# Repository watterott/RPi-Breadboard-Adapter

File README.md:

# RPi to Breadboard Adapter
Breadboard Adapter for all Raspberry Pi HAT compatible models (40pin connector).

* Open-Source and released under the [Creative Commons Attribution Share-Alike License](https://creativecommons.org/licenses/by-sa/4.0/).
* **[Documentation on learn.watterott.com](https://learn.watterott.com)**

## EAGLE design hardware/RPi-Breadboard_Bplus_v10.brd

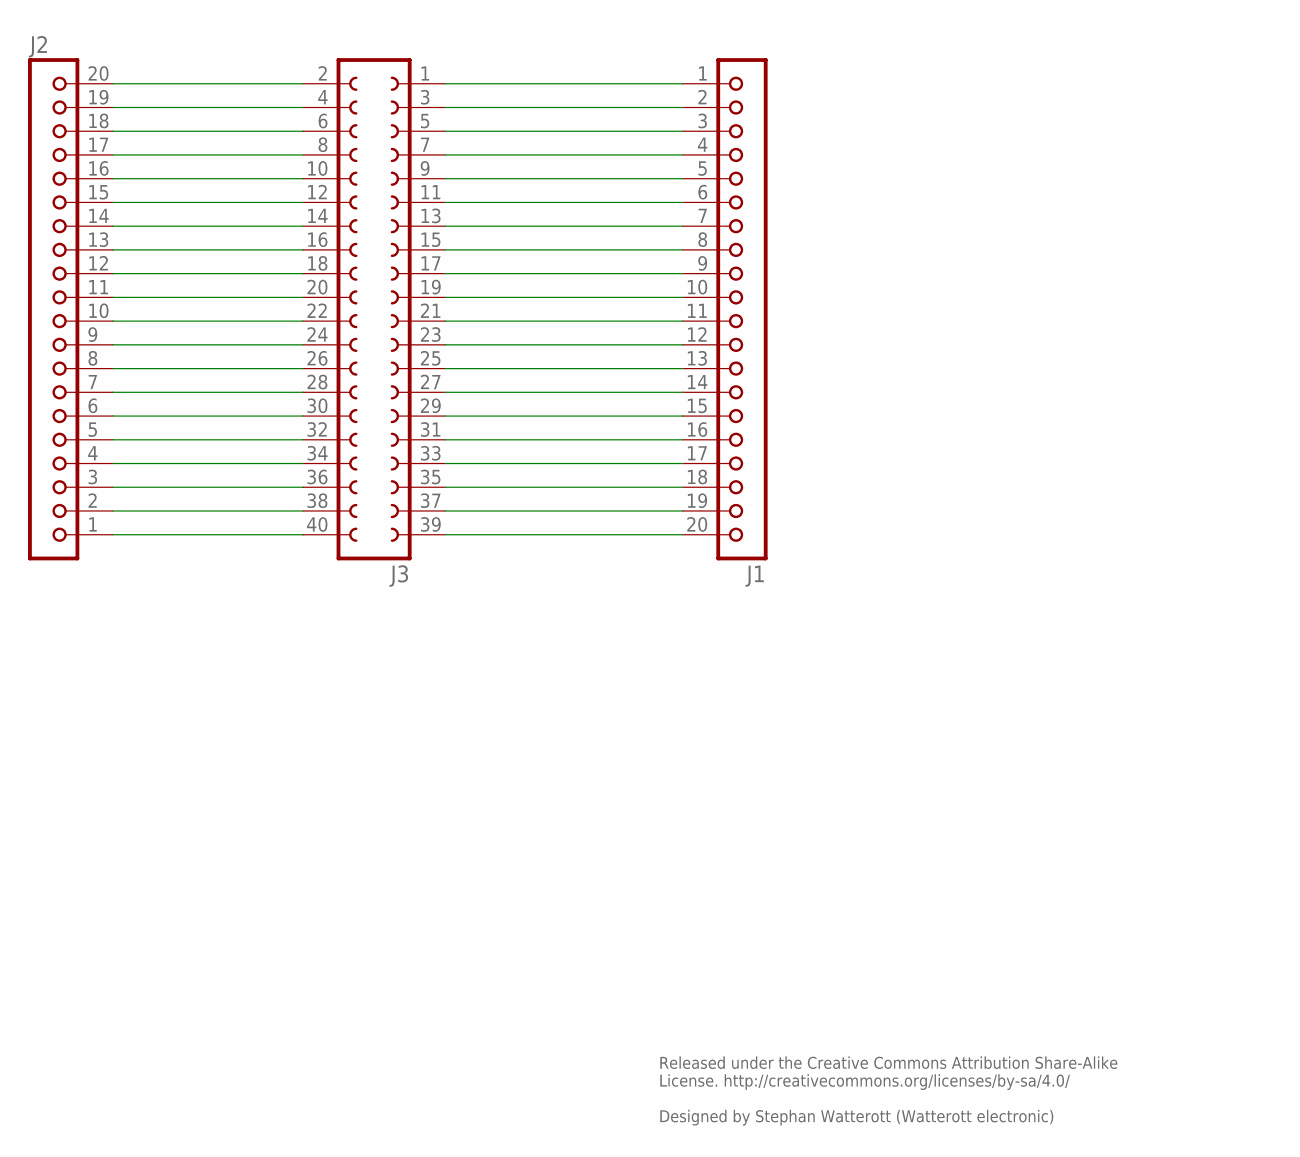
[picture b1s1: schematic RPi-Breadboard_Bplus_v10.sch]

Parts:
J1, J2: JBK20
J3: FE20-2

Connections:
5V: J1.1, J1.2, J3.1, J3.3
GND: J1.3, J1.7, J1.10, J1.15, J1.17, J2.1, J2.8, J2.16, J3.5, J3.10, J3.13, J3.19, J3.26, J3.29, J3.33, J3.40
unnamed: J1.4, J3.7
unnamed: J1.5, J3.9
unnamed: J1.6, J3.11
unnamed: J1.8, J3.15
unnamed: J1.9, J3.17
unnamed: J1.11, J3.21
unnamed: J1.12, J3.23
unnamed: J1.13, J3.25
unnamed: J1.14, J3.27
unnamed: J1.16, J3.31
unnamed: J1.18, J3.35
unnamed: J1.19, J3.37
unnamed: J1.20, J3.39
unnamed: J2.2, J3.38
unnamed: J2.3, J3.36
unnamed: J2.4, J3.34
unnamed: J2.5, J3.32
unnamed: J2.6, J3.30
unnamed: J2.7, J3.28
unnamed: J2.9, J3.24
unnamed: J2.10, J3.22
unnamed: J2.11, J3.20
unnamed: J2.12, J3.18
unnamed: J2.13, J3.16
unnamed: J2.14, J3.14
unnamed: J2.15, J3.12
unnamed: J2.17, J3.8
unnamed: J2.18, J3.6
unnamed: J2.19, J3.4
unnamed: J2.20, J3.2

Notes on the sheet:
Released under the Creative Commons Attribution Share-Alike License. http://creativecommons.org/licenses/by-sa/4.0/ Designed by Stephan Watterott (Watterott electronic)

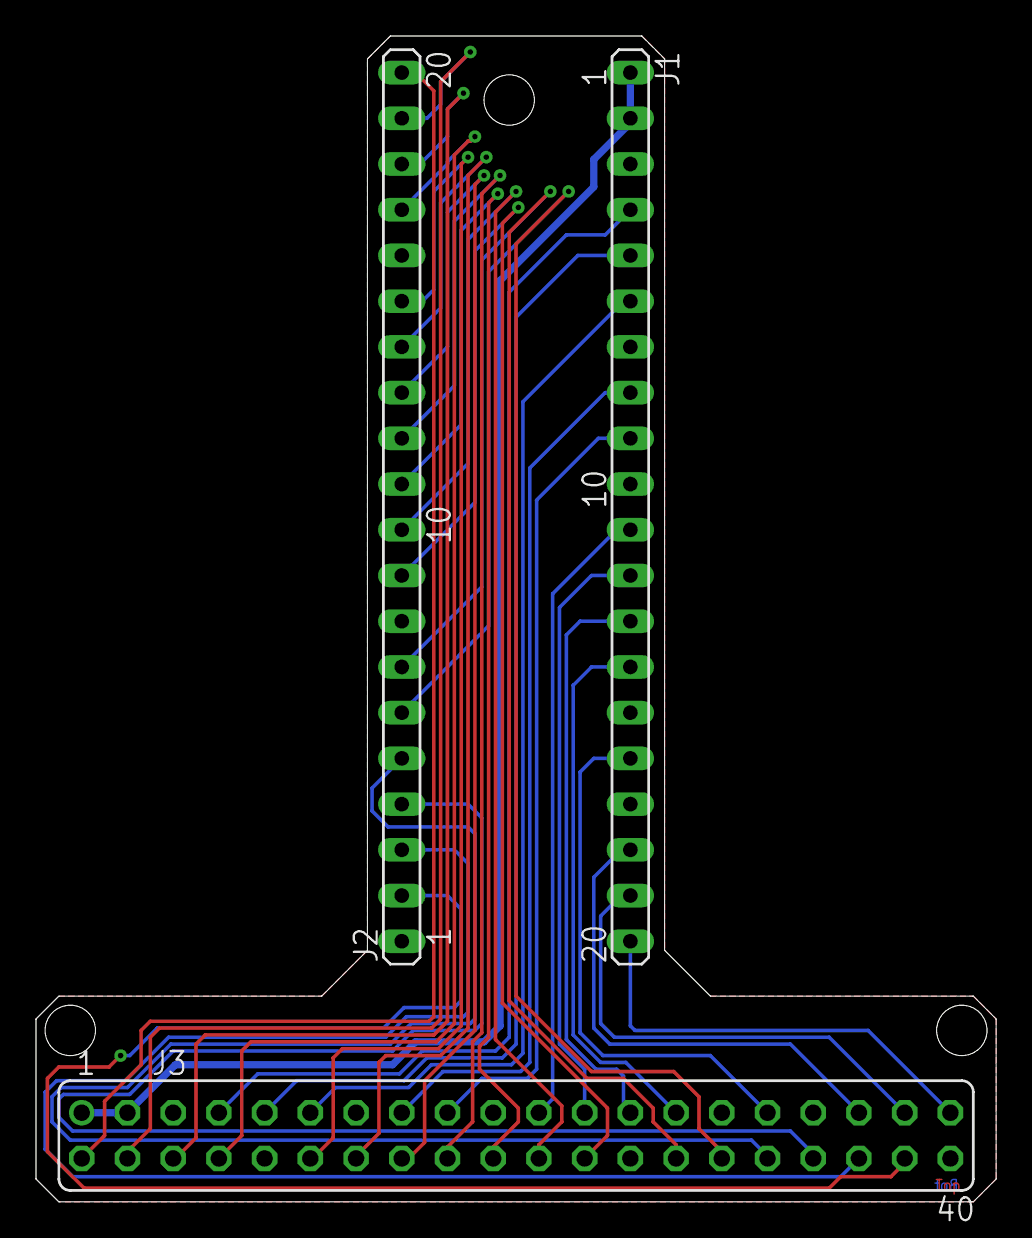
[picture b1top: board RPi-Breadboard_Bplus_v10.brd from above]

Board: 2 copper layers, 53.3 x 64.8 mm, 3 parts (0 on the bottom side), 32 nets.
